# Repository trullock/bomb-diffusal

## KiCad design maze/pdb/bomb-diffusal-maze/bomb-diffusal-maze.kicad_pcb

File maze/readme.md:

# Maze module

## Instructions

When armed, the maze will show a number of dots.
Correlate these dots with the maze maps in the instructions to identify the correct map.

Once ready press any key once.

The defuser must navigate the dot from its starting position to the end position shown on the map without colliding with any walls or the outer boundaries. Beware, these walls are not shown on the bomb itself.

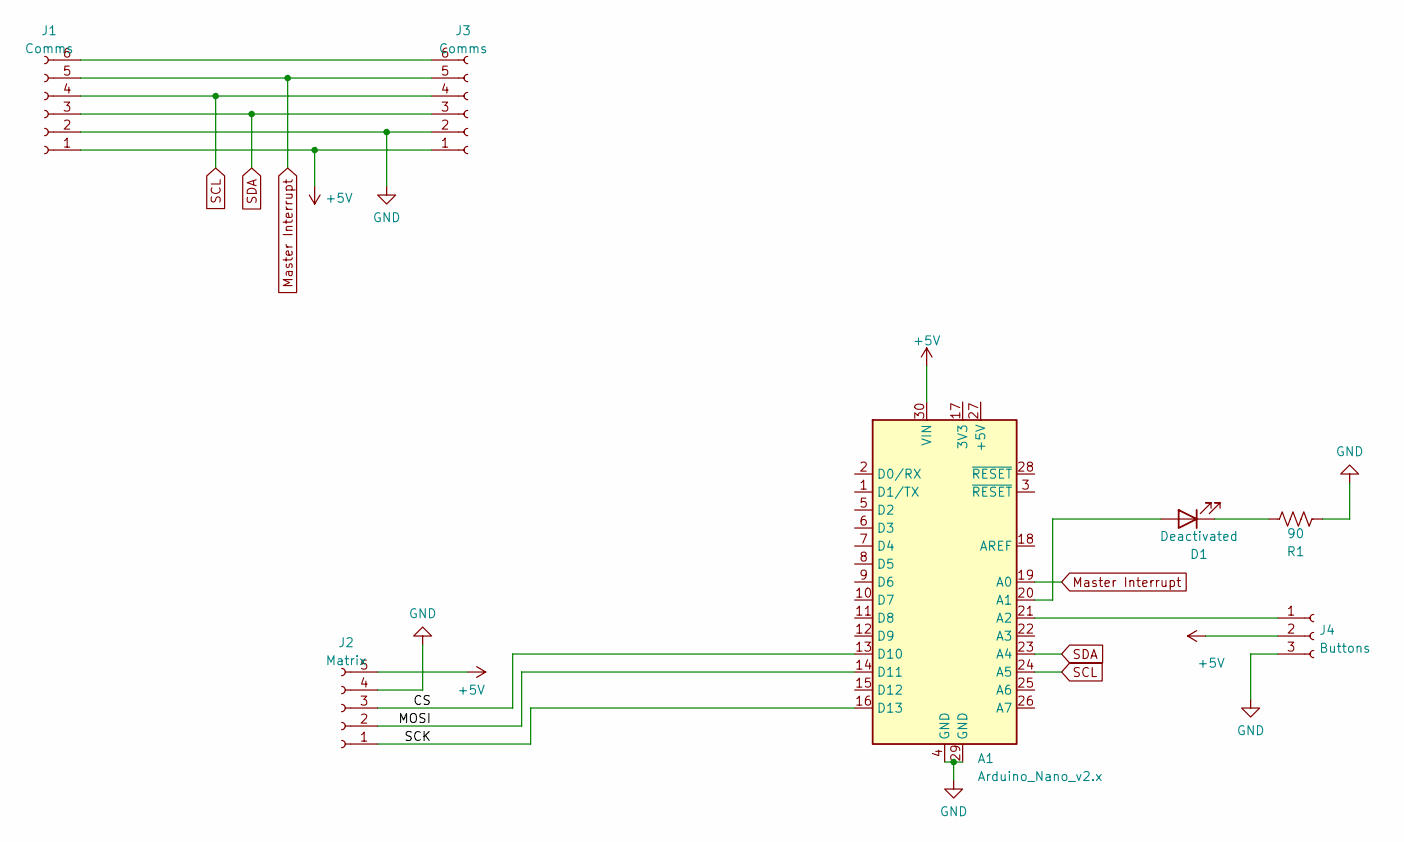
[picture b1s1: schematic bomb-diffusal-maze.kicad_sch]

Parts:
A1: Arduino_Nano_v2.x; Arduino_Nano
D1: Deactivated; PinHeader_1x02_P2.54mm_Vertical
J1, J3: Comms; JST_6P_1.25
J2: Matrix; PinHeader_1x05_P2.54mm_Vertical
J4: Buttons; PinHeader_1x03_P2.54mm_Vertical
R1: 90; R_Axial_DIN0309_L9.0mm_D3.2mm_P12.70mm_Horizontal

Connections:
+5V: A1.30 (VIN), J1.1, J2.5, J3.1, J4.2
/CS: A1.13 (D10), J2.3
/MOSI: A1.14 (D11), J2.2
/SCK: A1.16 (D13), J2.1
GND: A1.4 (GND), A1.29 (GND), J1.2, J2.4, J3.2, J4.3, R1.1
Master Interrupt: A1.19 (A0), J1.5, J3.5
unnamed: A1.20 (A1), D1.2 (A)
unnamed: A1.21 (A2), J4.1
unnamed: D1.1 (K), R1.2
unnamed: J1.6, J3.6
SCL: A1.24 (A5), J1.4, J3.4
SDA: A1.23 (A4), J1.3, J3.3

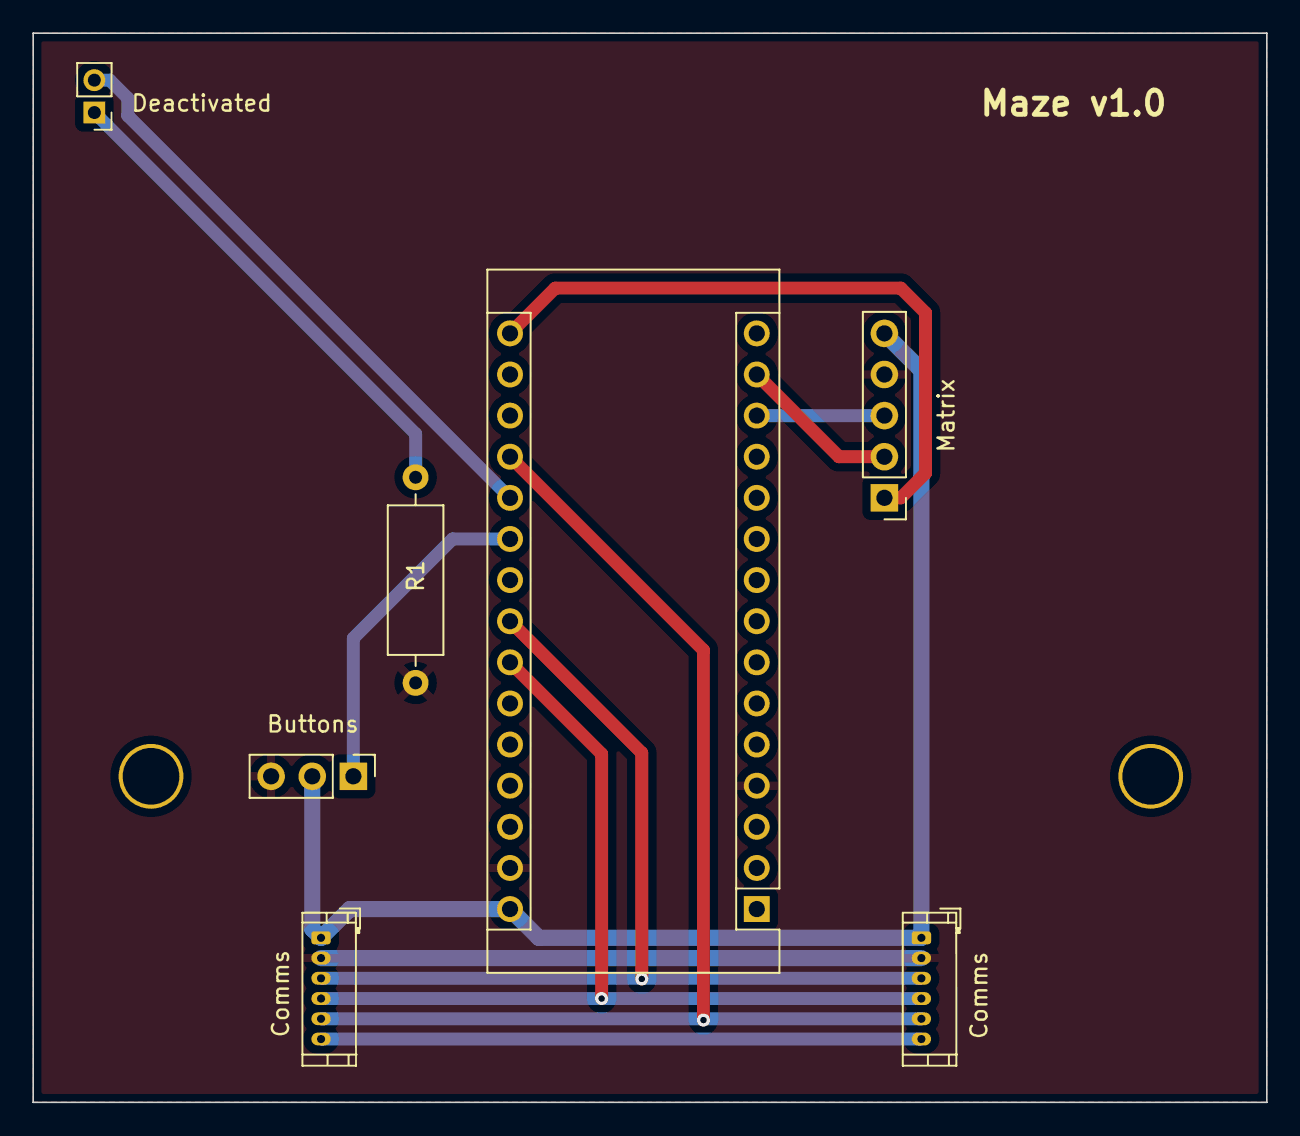
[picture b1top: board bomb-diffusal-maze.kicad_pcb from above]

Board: 2 copper layers, 76.2 x 66.0 mm, 7 parts (0 on the bottom side), 12 nets.

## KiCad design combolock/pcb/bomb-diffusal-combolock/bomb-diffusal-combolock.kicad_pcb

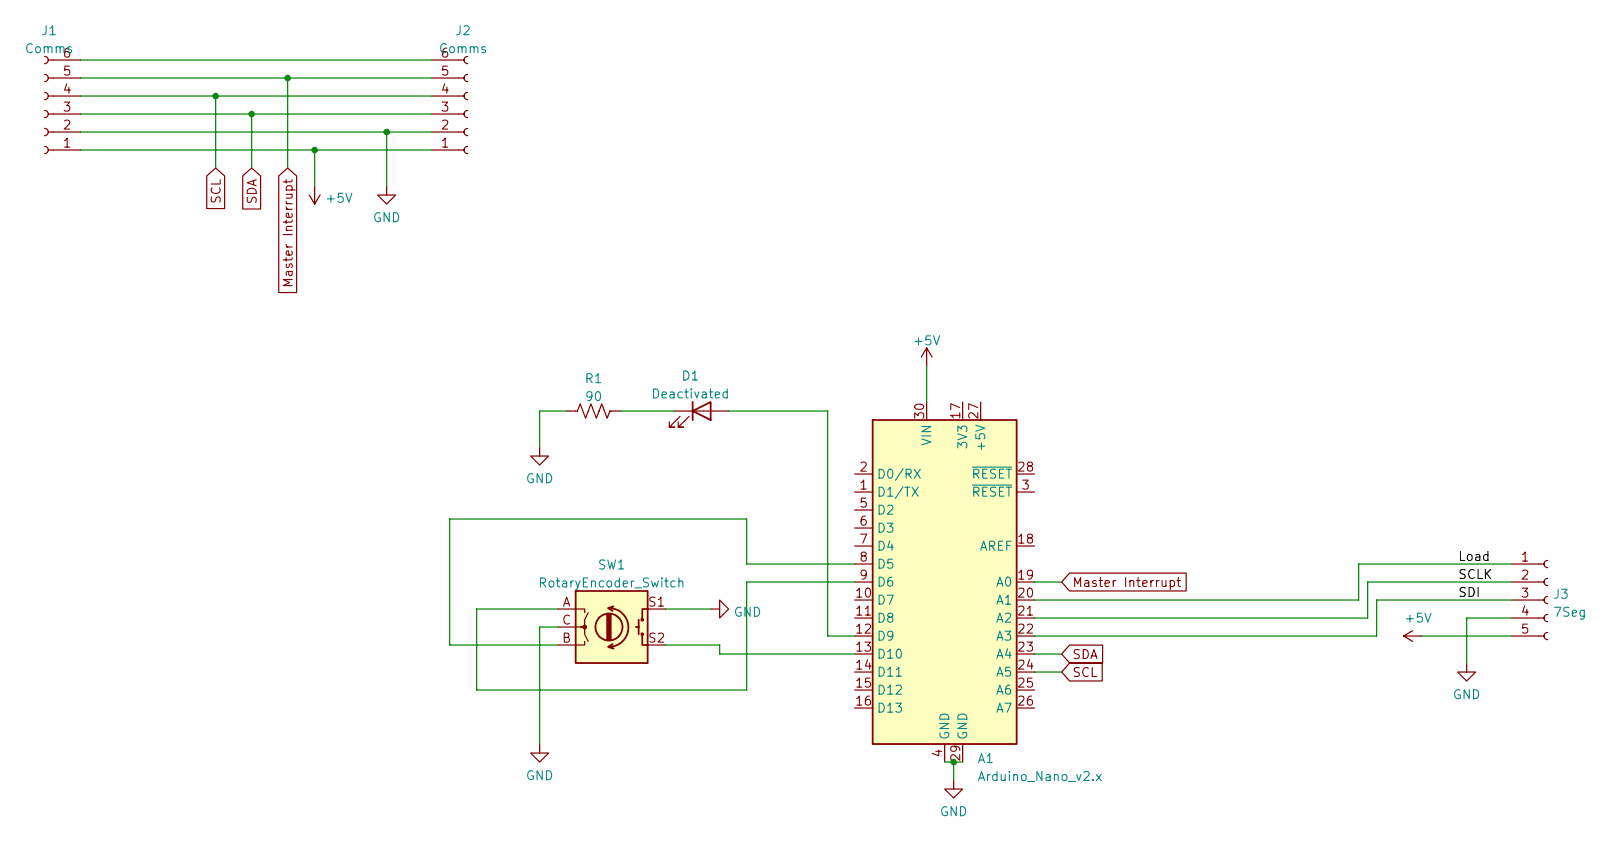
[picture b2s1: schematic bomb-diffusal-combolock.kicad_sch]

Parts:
A1: Arduino_Nano_v2.x; Arduino_Nano
D1: Deactivated; PinHeader_1x02_P2.54mm_Vertical
J1, J2: Comms; JST_6P_1.25
J3: 7Seg; PinHeader_1x05_P2.54mm_Vertical
R1: 90; R_Axial_DIN0309_L9.0mm_D3.2mm_P12.70mm_Horizontal
SW1: RotaryEncoder_Switch; RotaryEncoder_Alps_EC11E-Switch_Vertical_H20mm

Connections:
+5V: A1.30 (VIN), J1.1, J2.1, J3.5
/Load: A1.20 (A1), J3.1
/SCLK: A1.21 (A2), J3.2
/SDI: A1.22 (A3), J3.3
GND: A1.4 (GND), A1.29 (GND), J1.2, J2.2, J3.4, R1.1, SW1.C, SW1.S1
Master Interrupt: A1.19 (A0), J1.5, J2.5
unnamed: A1.8 (D5), SW1.B
unnamed: A1.9 (D6), SW1.A
unnamed: A1.12 (D9), D1.2 (A)
unnamed: D1.1 (K), R1.2
unnamed: J1.6, J2.6
unnamed: A1.13 (D10), SW1.S2
SCL: A1.24 (A5), J1.4, J2.4
SDA: A1.23 (A4), J1.3, J2.3

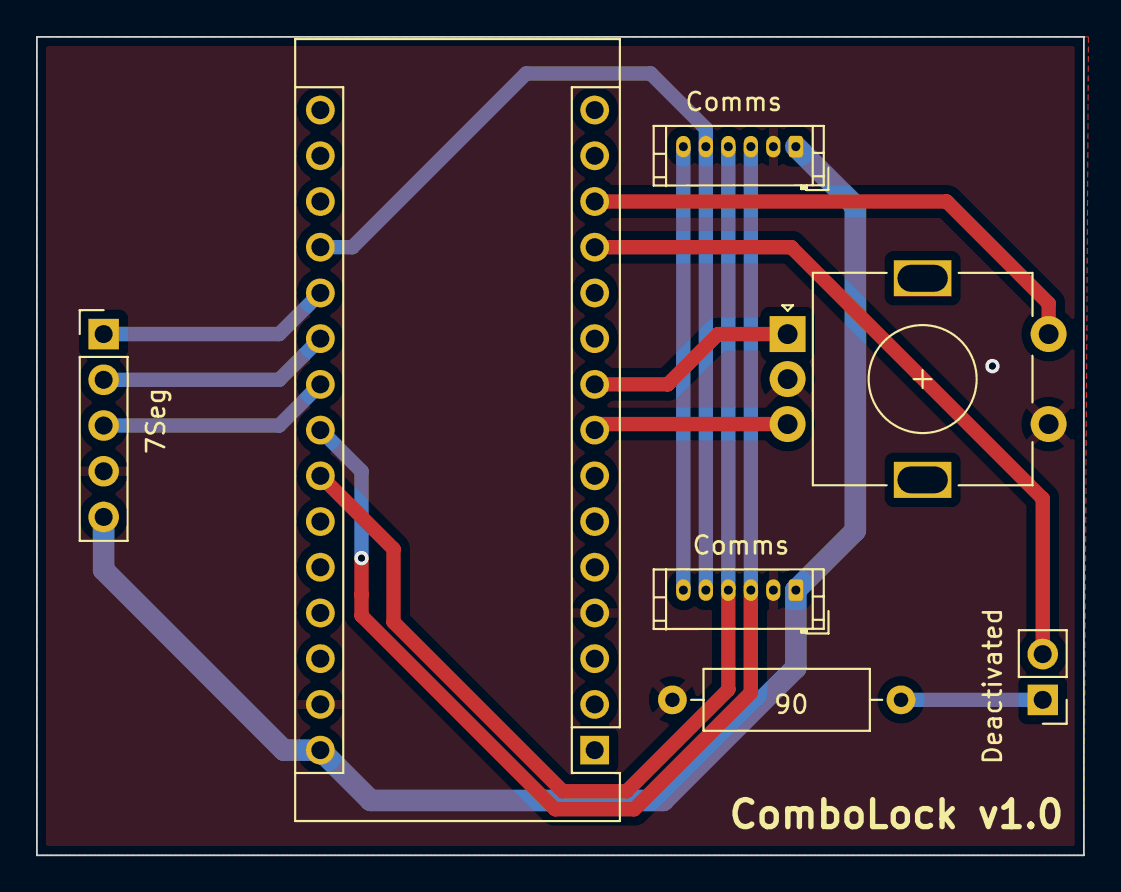
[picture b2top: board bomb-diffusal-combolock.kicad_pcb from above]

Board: 2 copper layers, 58.2 x 45.5 mm, 7 parts (0 on the bottom side), 14 nets.

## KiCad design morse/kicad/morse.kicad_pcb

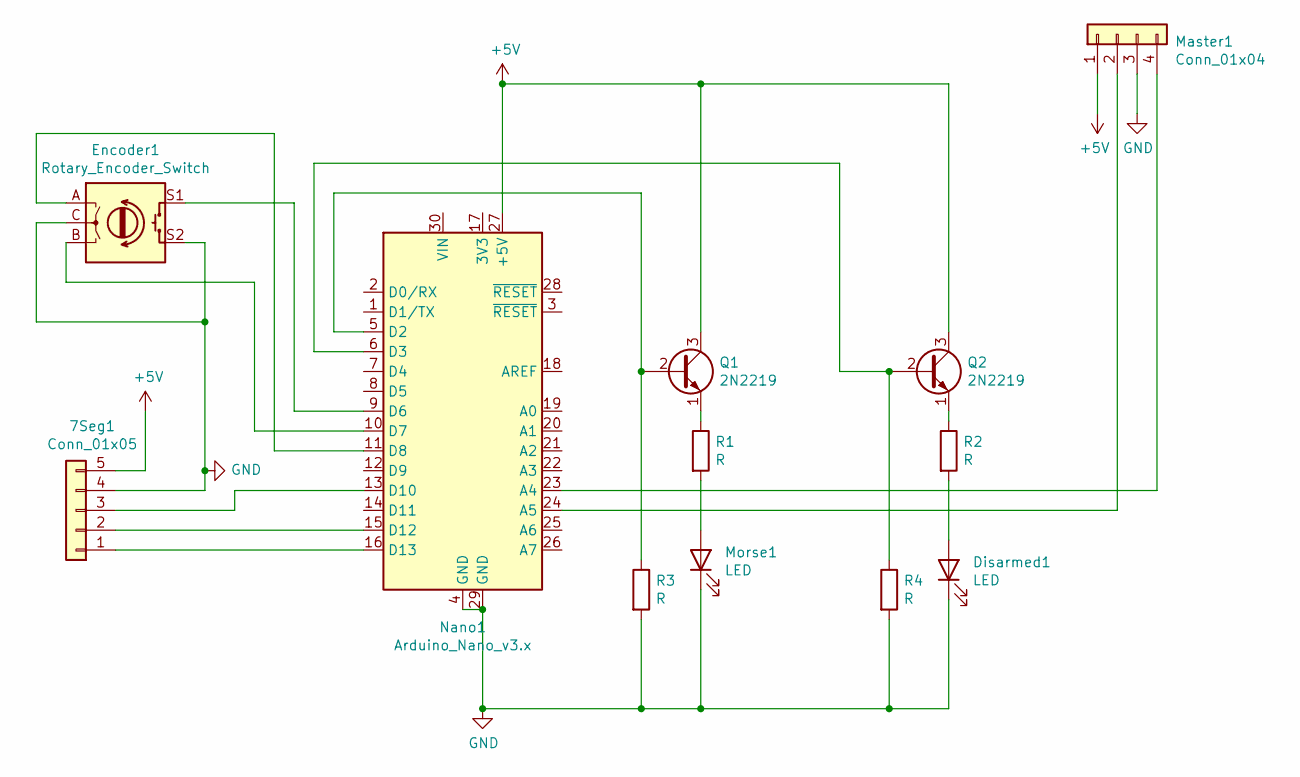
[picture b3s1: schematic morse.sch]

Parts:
7Seg1: Conn_01x05; PinHeader_1x05_P2.54mm_Vertical
Disarmed1: LED; LED_D5.0mm
Encoder1: Rotary_Encoder_Switch; RotaryEncoder_Alps_EC11E-Switch_Vertical_H20mm_CircularMoun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
Master1: Conn_01x04; PinHeader_1x04_P2.54mm_Vertical
Morse1: LED; LED_D10.0mm
Nano1: Arduino_Nano_v3.x; Arduino_Nano
Q1, Q2: 2N2219; TO-39-3
R1, R2, R3, R4: R; R_Axial_DIN0309_L9.0mm_D3.2mm_P12.70mm_Horizontal

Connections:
+5V: 7Seg1.5, Master1.1, Nano1.27 (+5V), Q1.3 (C), Q2.3 (C)
GND: 7Seg1.4, Disarmed1.1 (K), Encoder1.C, Encoder1.S2, Master1.3, Morse1.1 (K), Nano1.4 (GND), Nano1.29 (GND), R3.2, R4.2
unnamed: 7Seg1.1, Nano1.16 (D13)
unnamed: 7Seg1.2, Nano1.15 (D12)
unnamed: 7Seg1.3, Nano1.13 (D10)
unnamed: Disarmed1.2 (A), R2.2
unnamed: Encoder1.A, Nano1.11 (D8)
unnamed: Encoder1.B, Nano1.10 (D7)
unnamed: Encoder1.S1, Nano1.9 (D6)
unnamed: Master1.2, Nano1.24 (A5)
unnamed: Master1.4, Nano1.23 (A4)
unnamed: Morse1.2 (A), R1.2
unnamed: Nano1.5 (D2), Q1.2 (B), R3.1
unnamed: Nano1.6 (D3), Q2.2 (B), R4.1
unnamed: Q1.1 (E), R1.1
unnamed: Q2.1 (E), R2.1

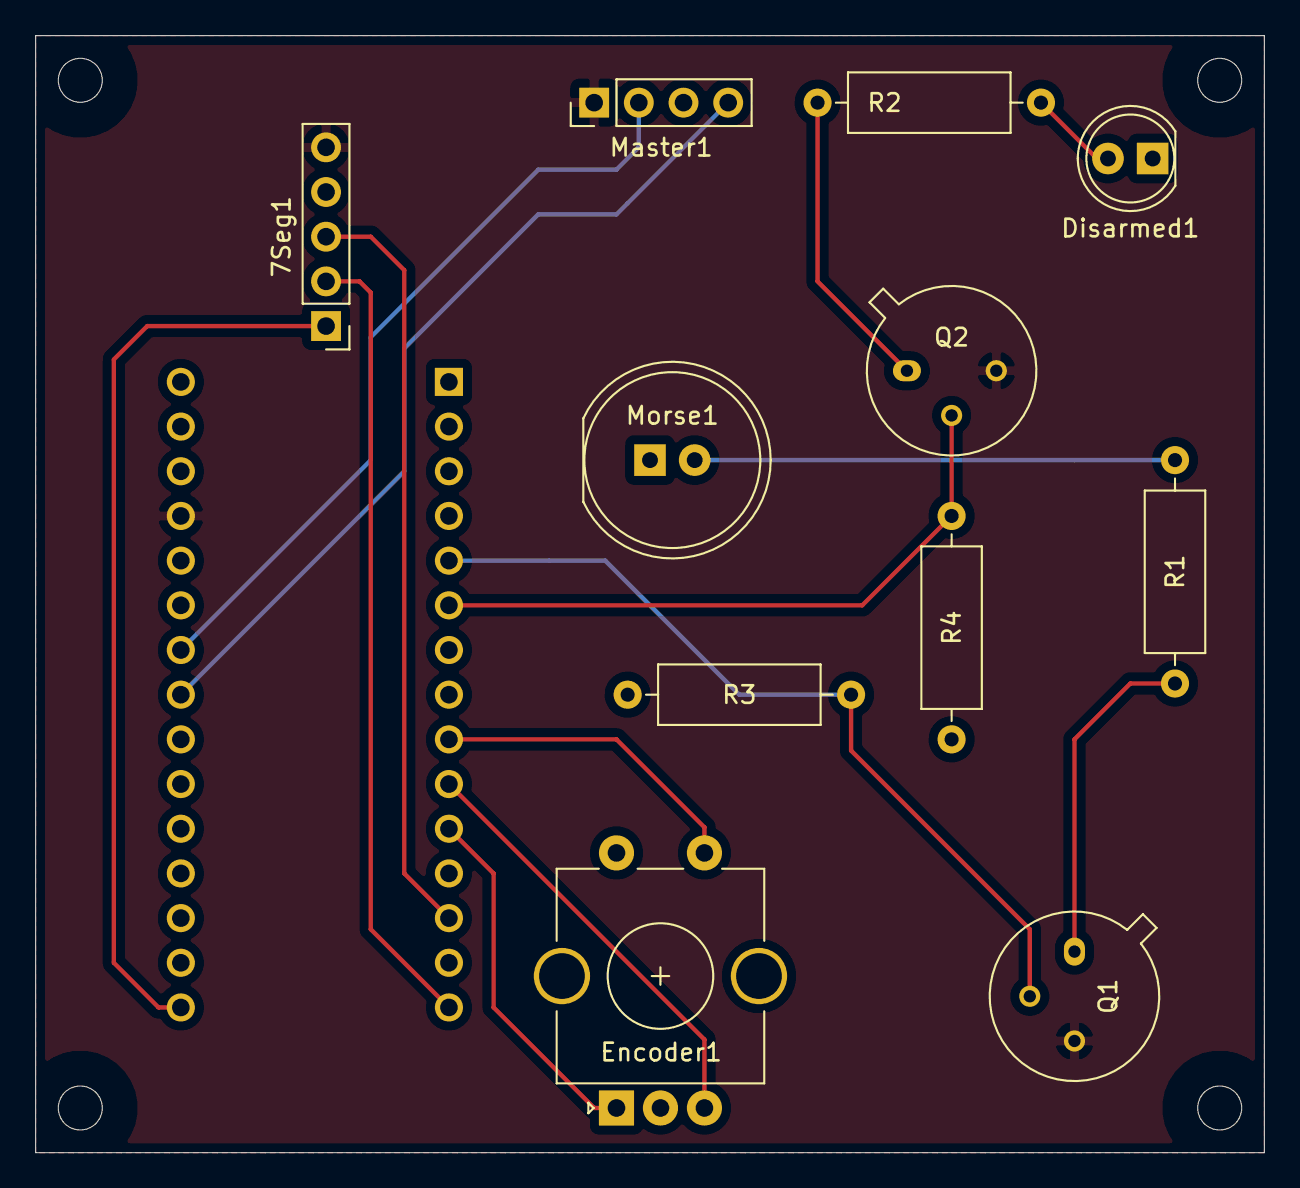
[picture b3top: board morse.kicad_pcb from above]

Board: 2 copper layers, 69.8 x 63.5 mm, 12 parts (1 on the bottom side), 16 nets.

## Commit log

2021-07-21 added basic master code, and started the morse module
2021-07-22 added command system to master and morse
2021-07-22 fixed arming procedure
2021-07-22 fixed gitignores, implemented morse difficulty, started adding notification support
2021-07-27 added maze beginnings
2021-07-27 added button class as abstraction
2021-07-29 started abstracting common slave code
2021-07-29 started porting button code
2021-07-29 migrated maze and master to platformio
2021-07-29 fixed build error
2021-07-30 converted master to pio
2021-07-30 symlink jct test
2021-07-30 made libs symlinks
2021-07-30 porting morse to pio
2021-07-30 fixed master i2c bugs, got morse working, added more striking
2021-07-30 fixed wire interrupt bug, made enocder and display work for morse
2021-07-30 removed old libs, updated maze and morse to use base.loop()
2021-07-30 fixed pio symlink issue in maze
2021-07-31 removed local files from git
2021-08-01 i2c improvements
2021-08-01 added kicad for morse, started adding memory module
2021-08-01 renamed kicad folder
2021-08-01 fixed symlinks
2021-08-02 improved i2c code, fixed memory build errors
2021-08-03 updating maze symlinks and added rotary encoder to kicad
2021-08-04 started adding knob module, started adding timing into master
2021-08-05 fixed build
2021-08-12 updating morse pcb layout
2021-08-15 removed files from git
2021-08-15 tidying master
2021-08-16 introduced needyslave, started implementing Capacitors
2021-08-17 removed sound from master
2021-08-17 fixed master time remaining bug
2021-08-20 playing with i2c software
2021-08-22 got sound fx working via I2S
2021-08-23 added more sfx
2021-08-24 fixed some dud sound files, some remain
2021-08-24 swapped out audio library
2021-08-24 tidied new sound lib usage2
2021-08-25 added test slave, implemented slave sfx requests
2021-08-25 tidied slave code
2021-08-26 fixing time bugs
2021-08-26 fixed countdown bugs
2021-08-26 implemented deactivation
2021-08-27 started adding lid awareness to master
2021-08-29 started adding unit tests to combolock
2021-08-30 started mocking arduino bits
2022-04-04 vscode
2022-04-04 commented 2nd capacitor
2022-04-04 refining capacitors and morse
2022-04-05 fixed rotary encoder
2022-04-06 improved sound, added combolock tests
2022-04-08 fixed capacitors knob
2022-04-09 tidying master and test-slave
2022-04-11 updated lives display
2022-04-11 adding time display to master
2022-04-12 fixed sounds
2022-04-12 fixed memory leak in sfx
2022-04-12 started adding played callbacks
2022-04-12 fixed sound callbacks
2023-02-23 lots of work on modules
2023-02-23 removed debug stuff from maze
2023-02-23 fixed maze ui bugs
2025-01-09 maze work
